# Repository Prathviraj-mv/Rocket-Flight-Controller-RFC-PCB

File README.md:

# Rocket-Flight-Controller-RFC-PCB
Custom Raspberry Pi Pico based Flight Controller PCB designed for model rockets, experimental aerospace systems, avionics testing, and embedded control applications.
# Rocket Flight Controller

Custom Raspberry Pi Pico based flight controller PCB for model rockets and embedded aerospace systems.
# Gallery

## Schematic

---

## PCB Layout

---

## Board Views

## Features

- RP2040 / Raspberry Pi Pico based
- 6 PWM servo outputs
- GPS interface
- IMU + BMP sensor interface
- RGB status LEDs
- Buzzer
- Voltage monitoring
- External servo power input
- On-board voltage regulation

## Hardware

- Raspberry Pi Pico
- AMS1117-5.0
- AMS1117-3.3
- RGB LEDs
- Piezo buzzer
- Screw terminals
- Servo headers

## Interfaces

| Interface | Purpose |
|---|---|
| PWM | Servo control |
| I2C | IMU / BMP sensors |
| UART | GPS module |
| ADC | Battery monitoring |

## Applications

- Rocket avionics
- Recovery systems
- Flight telemetry
- Sensor testing
- Embedded control projects

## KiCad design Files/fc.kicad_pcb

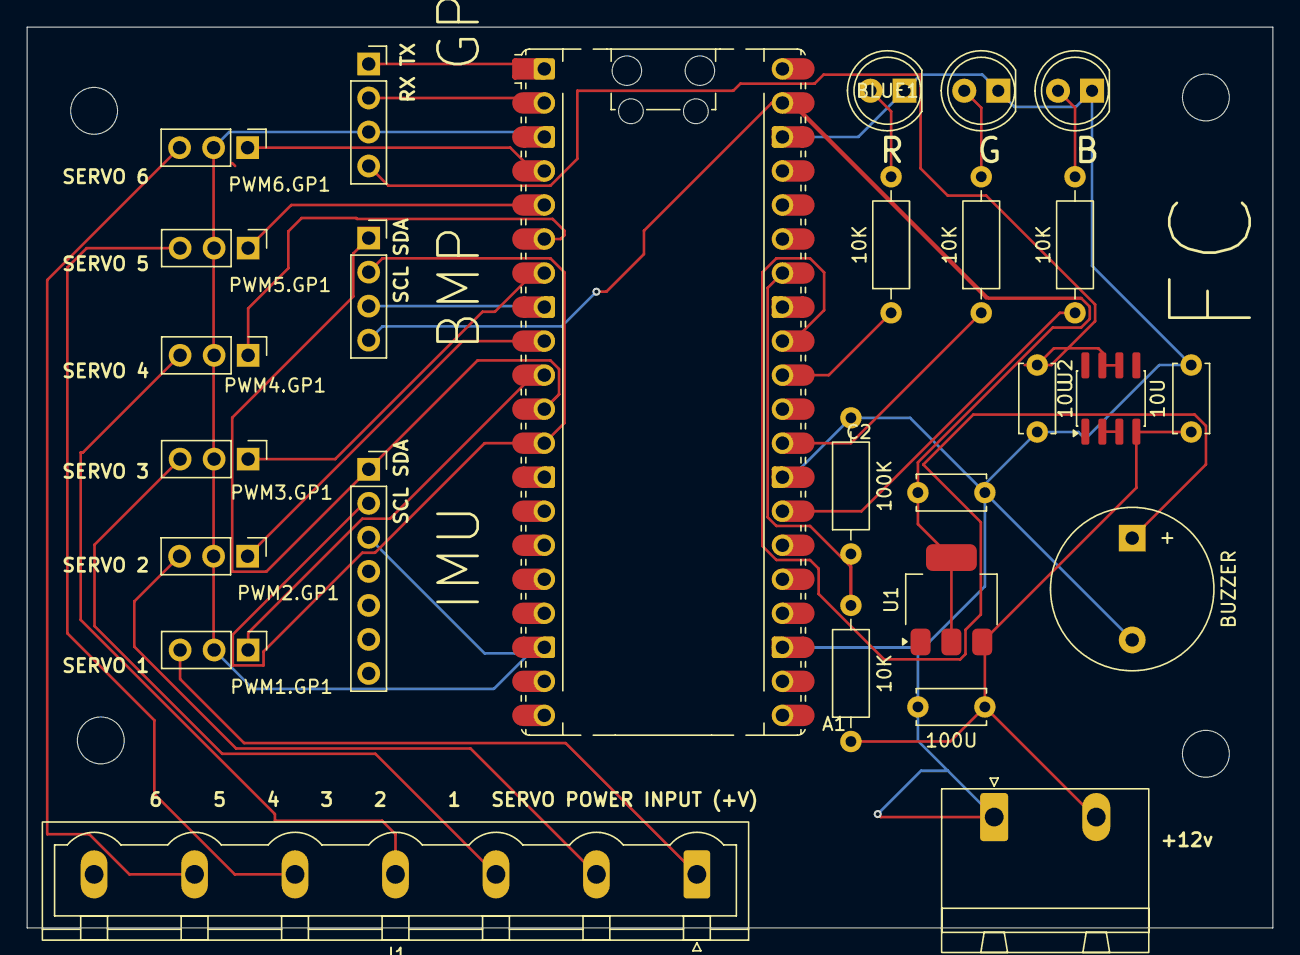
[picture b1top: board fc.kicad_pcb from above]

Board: 2 copper layers, 93.0 x 67.2 mm, 31 parts (0 on the bottom side), 23 nets.

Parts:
10K, 10K#2, 10K#3, 10K#4: 10k; R_Axial_DIN0207_L6.3mm_D2.5mm_P10.16mm_Horizontal
10U, 10U#2: C; C_Disc_D5.0mm_W2.5mm_P5.00mm
100K: 100k; R_Axial_DIN0207_L6.3mm_D2.5mm_P10.16mm_Horizontal
100U: 100u; C_Disc_D5.0mm_W2.5mm_P5.00mm
+12VPWR1: Screw_Terminal_01x02; PhoenixContact_GMSTBA_2,5_2-G-7,62_1x02_P7.62mm_Horizontal
A1: RaspberryPi_Pico; RaspberryPi_Pico_Common_Unspecified
BLUE1: LED; LED_D5.0mm
BUZZER: Buzzer; Buzzer_12x9.5RM7.6
C2: 20u; C_Disc_D5.0mm_W2.5mm_P5.00mm
Conn_01x04_Pin1: PRESSURE; PinSocket_1x04_P2.54mm_Vertical
Conn_01x04_Pin2: Conn_01x04_Socket; PinSocket_1x04_P2.54mm_Vertical
Conn_01x07_Pin1: GYRO+ACCEL; PinSocket_1x07_P2.54mm_Vertical
GREEN1: LED; LED_D5.0mm
H1, H2, H3, H4: MountingHole; MountingHole_3.5mm
J1: Screw_Terminal_01x06; PhoenixContact_GMSTBVA_2,5_7-G_1x07_P7.50mm_Vertical
LED1: RED; LED_D5.0mm
PWM1.GP1, PWM2.GP1, PWM3.GP1, PWM4.GP1, PWM5.GP1, PWM6.GP1: Conn_01x03_Pin; PinHeader_1x03_P2.54mm_Vertical
U1: AMS1117-3.3; SOT-223-3_TabPin2
U2: AMS1117CS-5.0; SOIC-8_3.9x4.9mm_P1.27mm

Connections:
+3.3V: A1.39 (VSYS), C2.1, Conn_01x04_Pin1.4, U1.2 (VO)
+5V: 10U#2.1, Conn_01x04_Pin2.4, Conn_01x07_Pin1.4, U2.2 (VO), U2.3 (VO), U2.6 (VO), U2.7 (VO)
+12V: 10K#3.1, 10U.1, 100U.1, +12VPWR1.2, U1.3 (VI), U2.4 (VI)
/PWM: A1.4 (GPIO2), A1.5 (GPIO3), A1.6 (GPIO4), A1.7 (GPIO5), A1.9 (GPIO6), A1.10 (GPIO7), PWM1.GP1.1, PWM2.GP1.1, PWM3.GP1.1, PWM4.GP1.1, PWM5.GP1.1, PWM6.GP1.1
/SCL: A1.12 (GPIO9), Conn_01x04_Pin1.2, Conn_01x07_Pin1.2
/SDA: A1.11 (GPIO8), Conn_01x04_Pin1.1, Conn_01x07_Pin1.1
GND: 10U.2, 10U#2.2, 100K.2, 100U.2, +12VPWR1.1, A1.3 (GND), A1.8 (GND), A1.13 (GND), A1.18 (GND), A1.23 (GND), A1.28 (GND), A1.38 (GND), BLUE1.1 (K), BUZZER.2 (-), C2.2, Conn_01x04_Pin1.3, Conn_01x04_Pin2.3, Conn_01x07_Pin1.3, GREEN1.1 (K), LED1.1 (K), PWM1.GP1.2, PWM2.GP1.2, PWM3.GP1.2, PWM4.GP1.2, PWM5.GP1.2, PWM6.GP1.2, U1.1 (GND), U2.1 (GND)
unnamed: A1.1 (GPIO0), Conn_01x04_Pin2.1
unnamed: A1.2 (GPIO1), Conn_01x04_Pin2.2
unnamed: 10K#4.1, A1.27 (GPIO21)
unnamed: 10K.1, A1.29 (GPIO22)
unnamed: 10K#2.1, A1.31 (GPIO26_ADC0)
unnamed: A1.32 (GPIO27_ADC1), BUZZER.1 (+)
unnamed: 10K#3.2, 100K.1, A1.34 (GPIO28_ADC2)
unnamed: 10K#2.2, BLUE1.2 (A)
unnamed: 10K.2, GREEN1.2 (A)
unnamed: J1.1, PWM1.GP1.3
unnamed: J1.2, PWM2.GP1.3
unnamed: J1.3, PWM3.GP1.3
unnamed: J1.4, PWM4.GP1.3
unnamed: J1.5, PWM5.GP1.3
unnamed: J1.6, PWM6.GP1.3
unnamed: 10K#4.2, LED1.2 (A)
